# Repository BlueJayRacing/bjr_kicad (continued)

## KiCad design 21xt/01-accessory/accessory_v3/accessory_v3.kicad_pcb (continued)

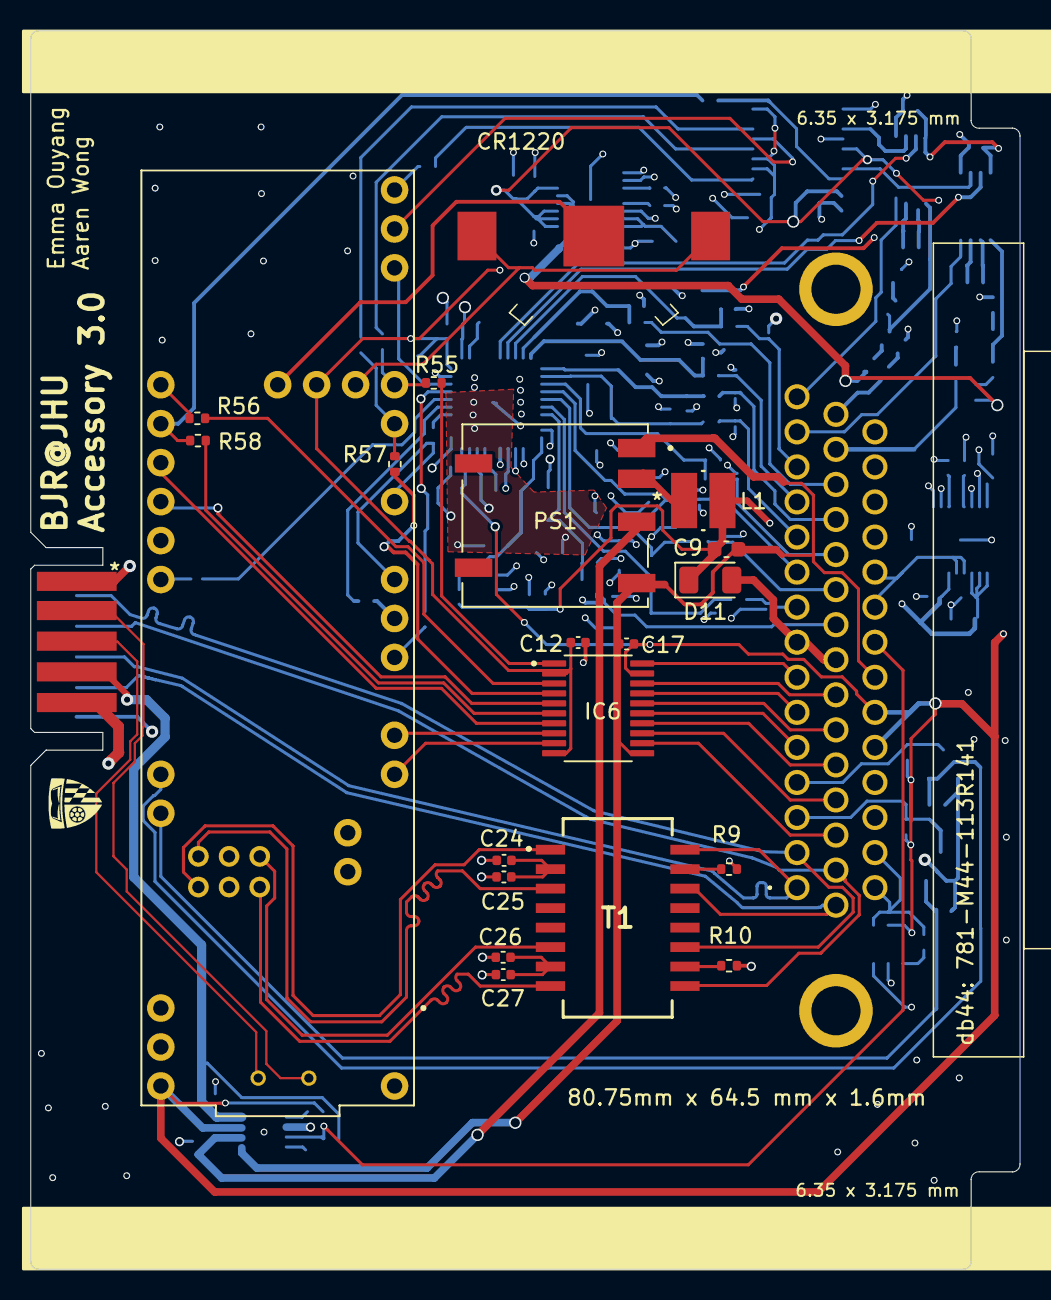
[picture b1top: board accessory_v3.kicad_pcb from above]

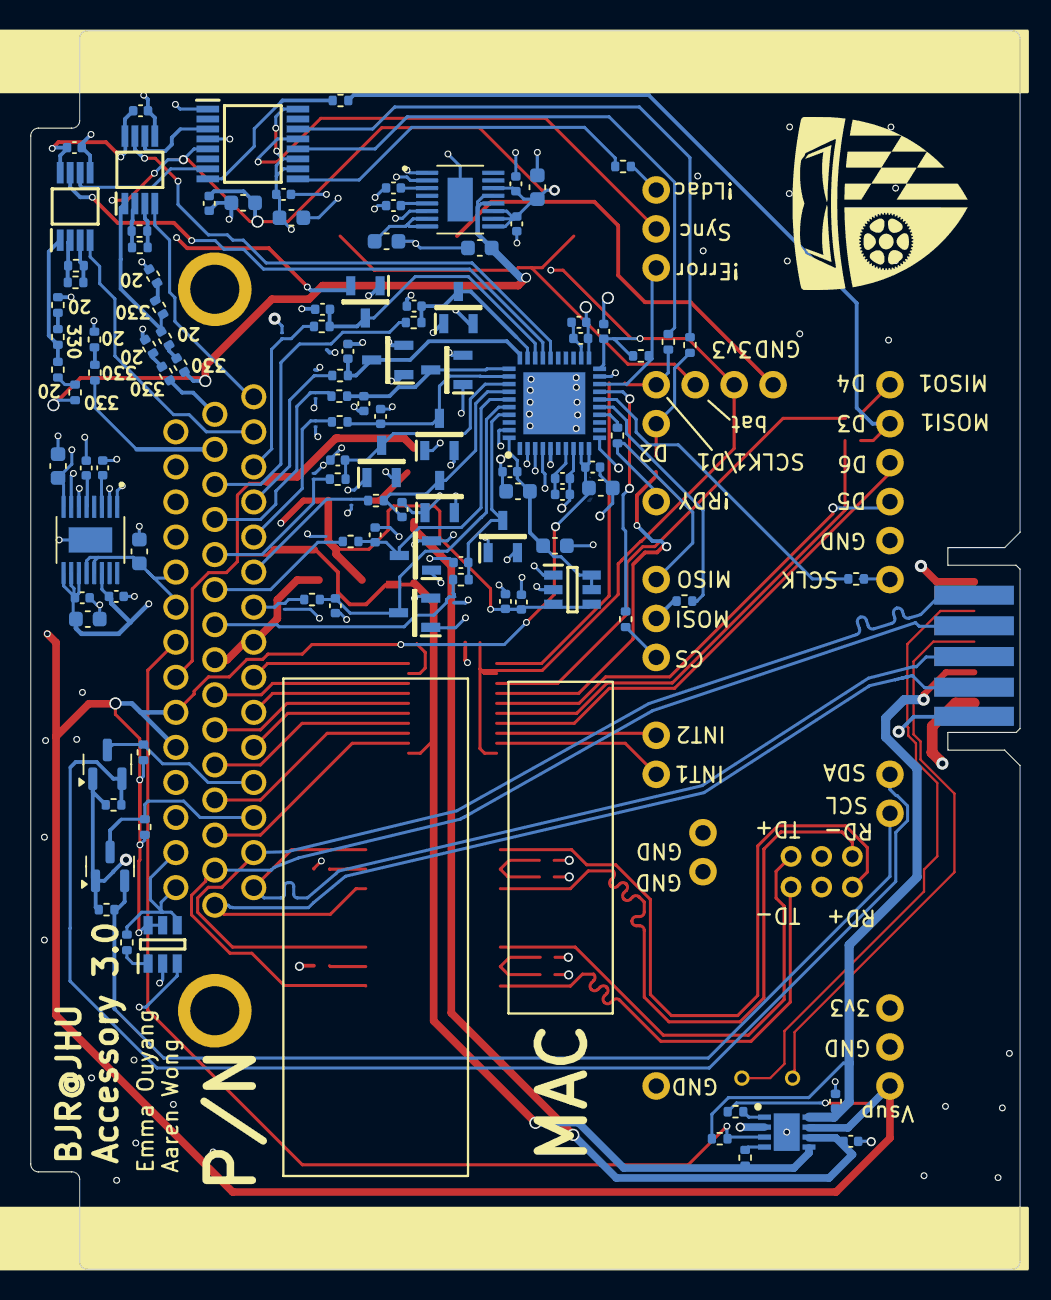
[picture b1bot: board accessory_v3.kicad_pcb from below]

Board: 4 copper layers, 64.5 x 80.8 mm, 141 parts (118 on the bottom side), 121 nets.

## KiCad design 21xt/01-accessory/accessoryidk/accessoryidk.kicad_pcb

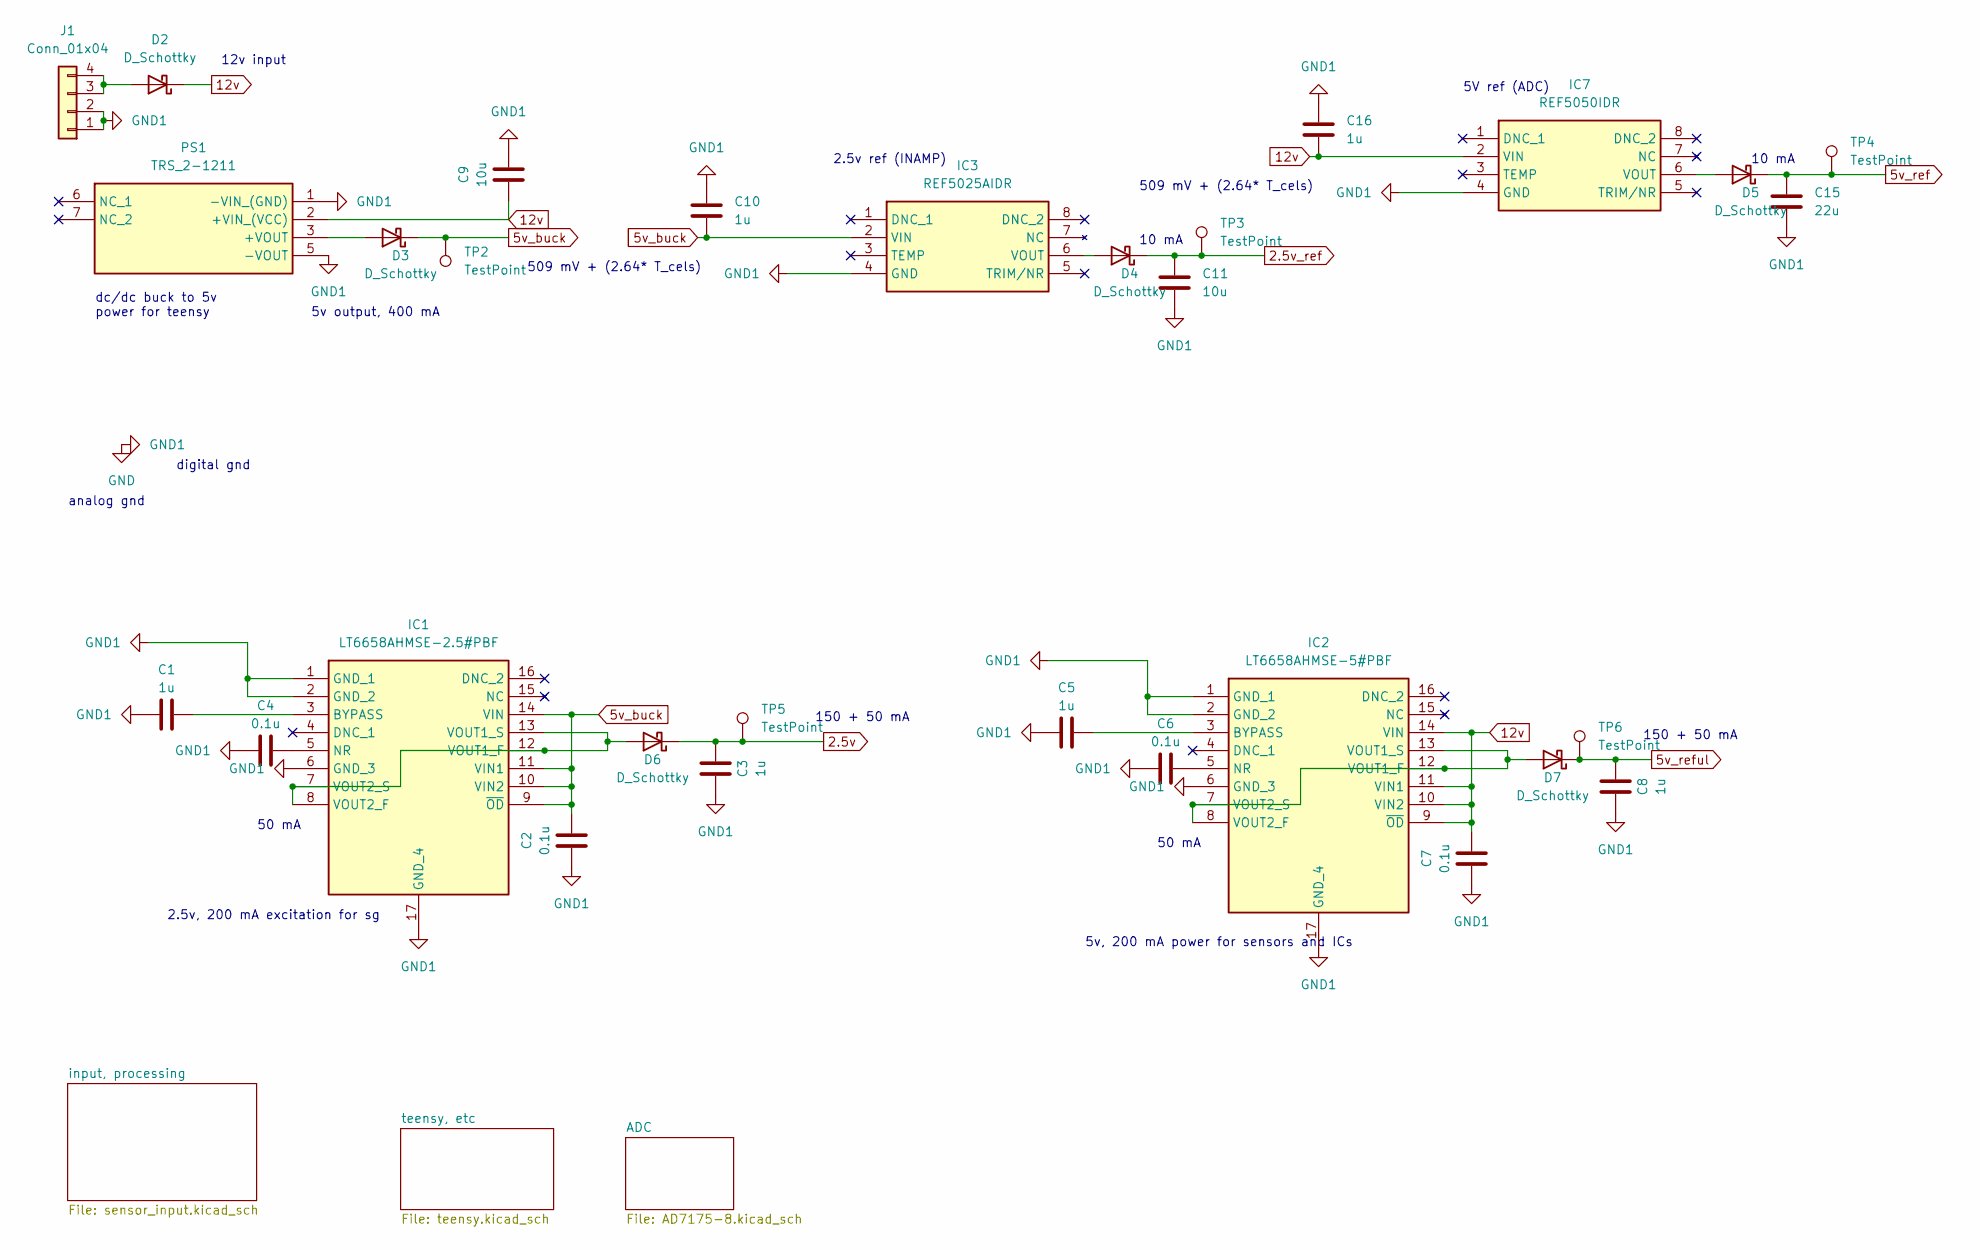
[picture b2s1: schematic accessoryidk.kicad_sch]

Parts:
C1, C3, C5, C8, C10, C16: 1u; C_0603_1608Metric
C2, C4, C6, C7: 0.1u; C_0603_1608Metric
C9: 10u; C_1206_3216Metric
C11: 10u; C_0603_1608Metric
C15: 22u; C_0603_1608Metric
D2: D_Schottky; D_1206_3216Metric
D3, D4, D5, D6, D7: D_Schottky; D_0603_1608Metric
IC1: LT6658AHMSE-2.5#PBF; SOP50P490X110-17N; Mouser Part Number 584-LT6658AHMSE5PBF
IC2: LT6658AHMSE-5#PBF; SOP50P490X110-17N; Mouser Part Number 584-LT6658AHMSE5PBF
IC3: REF5025AIDR; SOIC127P599X175-8N; Mouser Part Number 595-REF5050IDR
IC7: REF5050IDR; SOIC127P599X175-8N; Mouser Part Number 595-REF5050IDR
J1: Conn_01x04; JST_EH_B4B-EH-A_1x04_P2.50mm_Vertical
PS1: TRS_2-1211; CONV_TRS_2-2419; Mouser Part Number 495-TRS2-1211
TP2, TP3, TP4, TP5, TP6: TestPoint; TestPoint_Pad_2.0x2.0mm

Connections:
2.5v: C3.2, D6.1 (K), TP5.1; also elsewhere on the board
2.5v_ref: C11.1, D4.1 (K), TP3.1; also elsewhere on the board
5v_buck: C2.2, C10.1, D3.1 (K), IC1.9 (~OD), IC1.10 (VIN2), IC1.11 (VIN1), IC1.14 (VIN), IC3.2 (VIN), TP2.1; also elsewhere on the board
5v_ref: C15.1, D5.1 (K), TP4.1; also elsewhere on the board
5v_reful: C8.2, D7.1 (K), TP6.1; also elsewhere on the board
12v: C7.2, C9.1, C16.1, D2.1 (K), IC2.9 (~OD), IC2.10 (VIN2), IC2.11 (VIN1), IC2.14 (VIN), IC7.2 (VIN), PS1.2 (+VIN_(VCC)); also elsewhere on the board
unnamed: D2.2 (A), J1.3, J1.4
unnamed: D3.2 (A), PS1.3 (+VOUT)
unnamed: D4.2 (A), IC3.6 (VOUT)
unnamed: D5.2 (A), IC7.6 (VOUT)
unnamed: D6.2 (A), IC1.7 (VOUT2_S), IC1.8 (VOUT2_F), IC1.12 (VOUT1_F), IC1.13 (VOUT1_S)
unnamed: D7.2 (A), IC2.7 (VOUT2_S), IC2.8 (VOUT2_F), IC2.12 (VOUT1_F), IC2.13 (VOUT1_S)
unnamed: C1.2, IC1.3 (BYPASS)
unnamed: C4.2, IC1.5 (NR)
unnamed: C5.2, IC2.3 (BYPASS)
unnamed: C6.2, IC2.5 (NR)
usb_gnd: C1.1, C2.1, C3.1, C4.1, C5.1, C6.1, C7.1, C8.1, C9.2, C10.2, C11.2, C15.2, C16.2, IC1.1 (GND_1), IC1.2 (GND_2), IC1.6 (GND_3), IC1.17 (GND_4), IC2.1 (GND_1), IC2.2 (GND_2), IC2.6 (GND_3), IC2.17 (GND_4), IC3.4 (GND), IC7.4 (GND), J1.1, J1.2, PS1.1 (-VIN_(GND)), PS1.5 (-VOUT); also elsewhere on the board

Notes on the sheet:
2.5v, 200 mA excitation for sg
150 + 50 mA
50 mA
10 mA
5V ref (ADC)
12v input
5v, 200 mA power for sensors and ICs
2.5v ref (INAMP)
digital gnd
analog gnd
dc/dc buck to 5v power for teensy
5v output, 400 mA
509 mV + (2.64* T_cels)

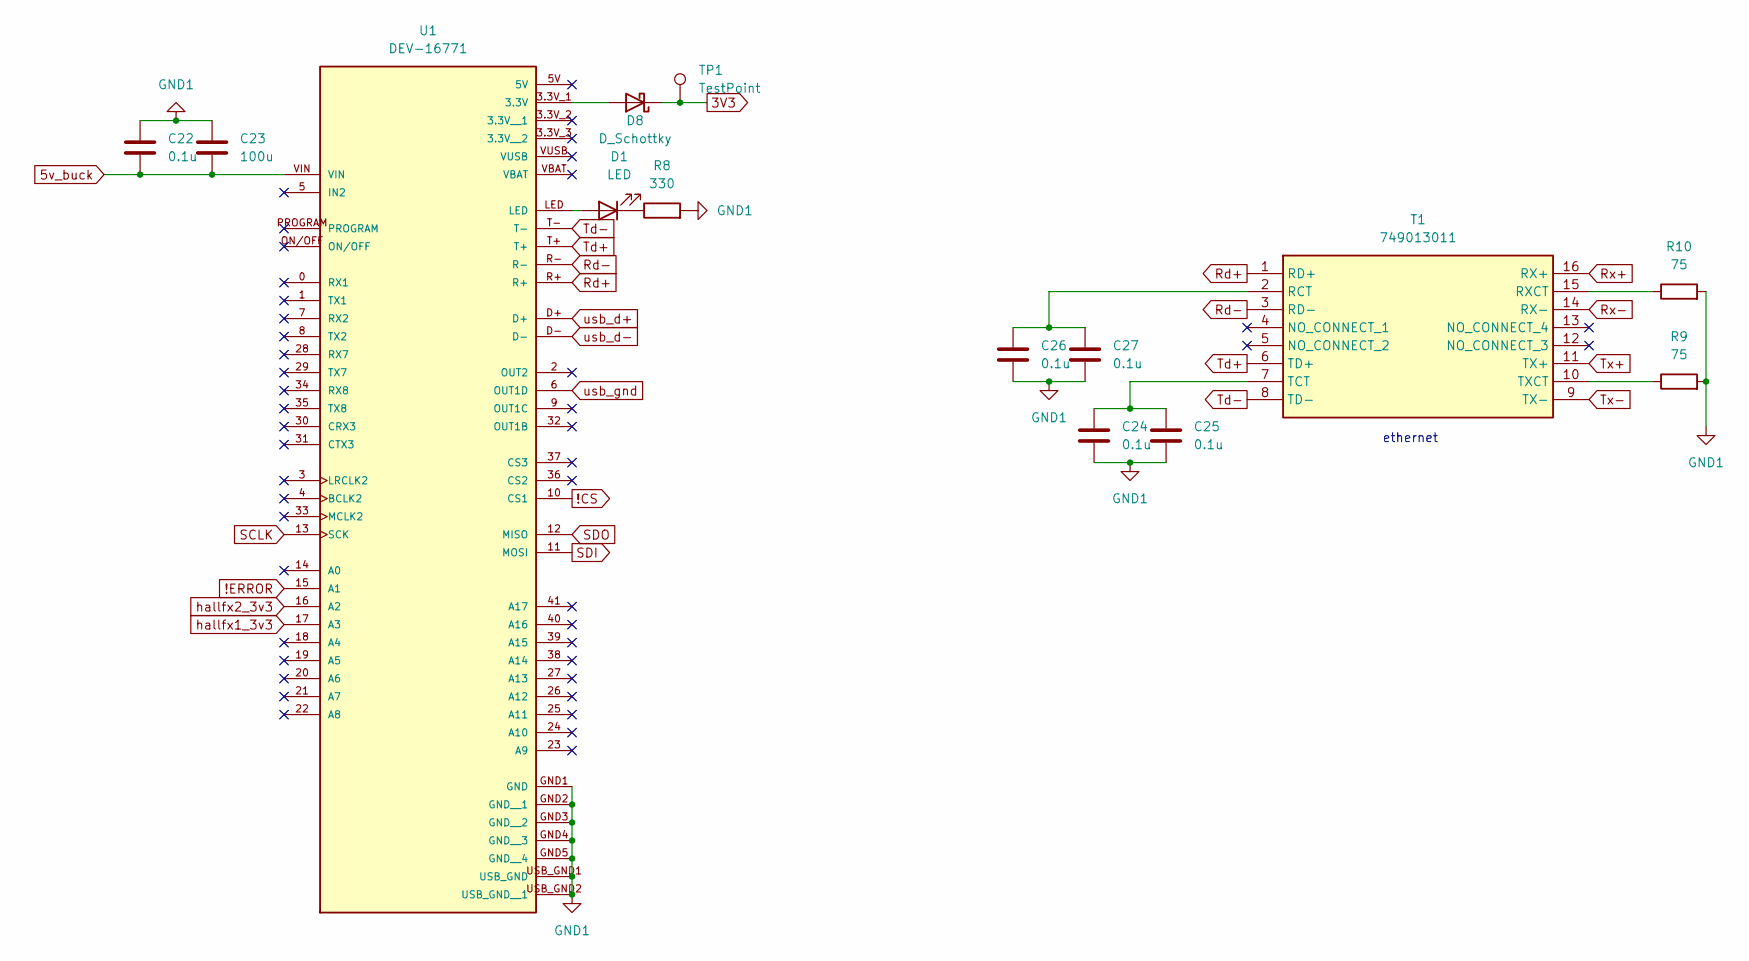
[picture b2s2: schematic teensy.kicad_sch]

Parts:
C22, C24, C25, C26, C27: 0.1u; C_0603_1608Metric
C23: 100u; C_1206_3216Metric
D1: LED; D_0603_1608Metric
D8: D_Schottky; D_0603_1608Metric
R8: 330; R_0603_1608Metric
R9, R10: 75; R_0603_1608Metric
T1: 749013011; Mouser Part Number 710-749013011
TP1: TestPoint; TestPoint_Pad_2.0x2.0mm
U1: DEV-16771; MODULE_DEV-16771; PARTREV 4.1

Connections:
3V3: D8.1 (K), TP1.1; also elsewhere on the board
5v_buck: C22.2, C23.2, U1.VIN; also elsewhere on the board
!CS: U1.10 (CS1); also elsewhere on the board
!ERROR: U1.15 (A1); also elsewhere on the board
unnamed: D1.2 (A), U1.LED
unnamed: D1.1 (K), R8.1
unnamed: D8.2 (A), U1.3.3V_1 (3.3V)
unnamed: C26.1, C27.1, T1.2 (RCT)
unnamed: R10.1, T1.15 (RXCT)
unnamed: C24.1, C25.1, T1.7 (TCT)
unnamed: R9.1, T1.10 (TXCT)
Rd+: T1.1 (RD+), U1.R+
Rd-: T1.3 (RD-), U1.R-
Rx+: T1.16 (RX+); also elsewhere on the board
Rx-: T1.14 (RX-); also elsewhere on the board
SCLK: U1.13 (SCK); also elsewhere on the board
SDI: U1.11 (MOSI); also elsewhere on the board
SDO: U1.12 (MISO); also elsewhere on the board
Td+: T1.6 (TD+), U1.T+
Td-: T1.8 (TD-), U1.T-
Tx+: T1.11 (TX+); also elsewhere on the board
Tx-: T1.9 (TX-); also elsewhere on the board
usb_d+: U1.D+; also elsewhere on the board
usb_d-: U1.D-; also elsewhere on the board
usb_gnd: C22.1, C23.1, C24.2, C25.2, C26.2, C27.2, R8.2, R9.2, R10.2, U1.6 (OUT1D), U1.GND1 (GND), U1.GND2 (GND__1), U1.GND3 (GND__2), U1.GND4 (GND__3), U1.GND5 (GND__4), U1.USB_GND1 (USB_GND), U1.USB_GND2 (USB_GND__1); also elsewhere on the board

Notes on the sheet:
ethernet

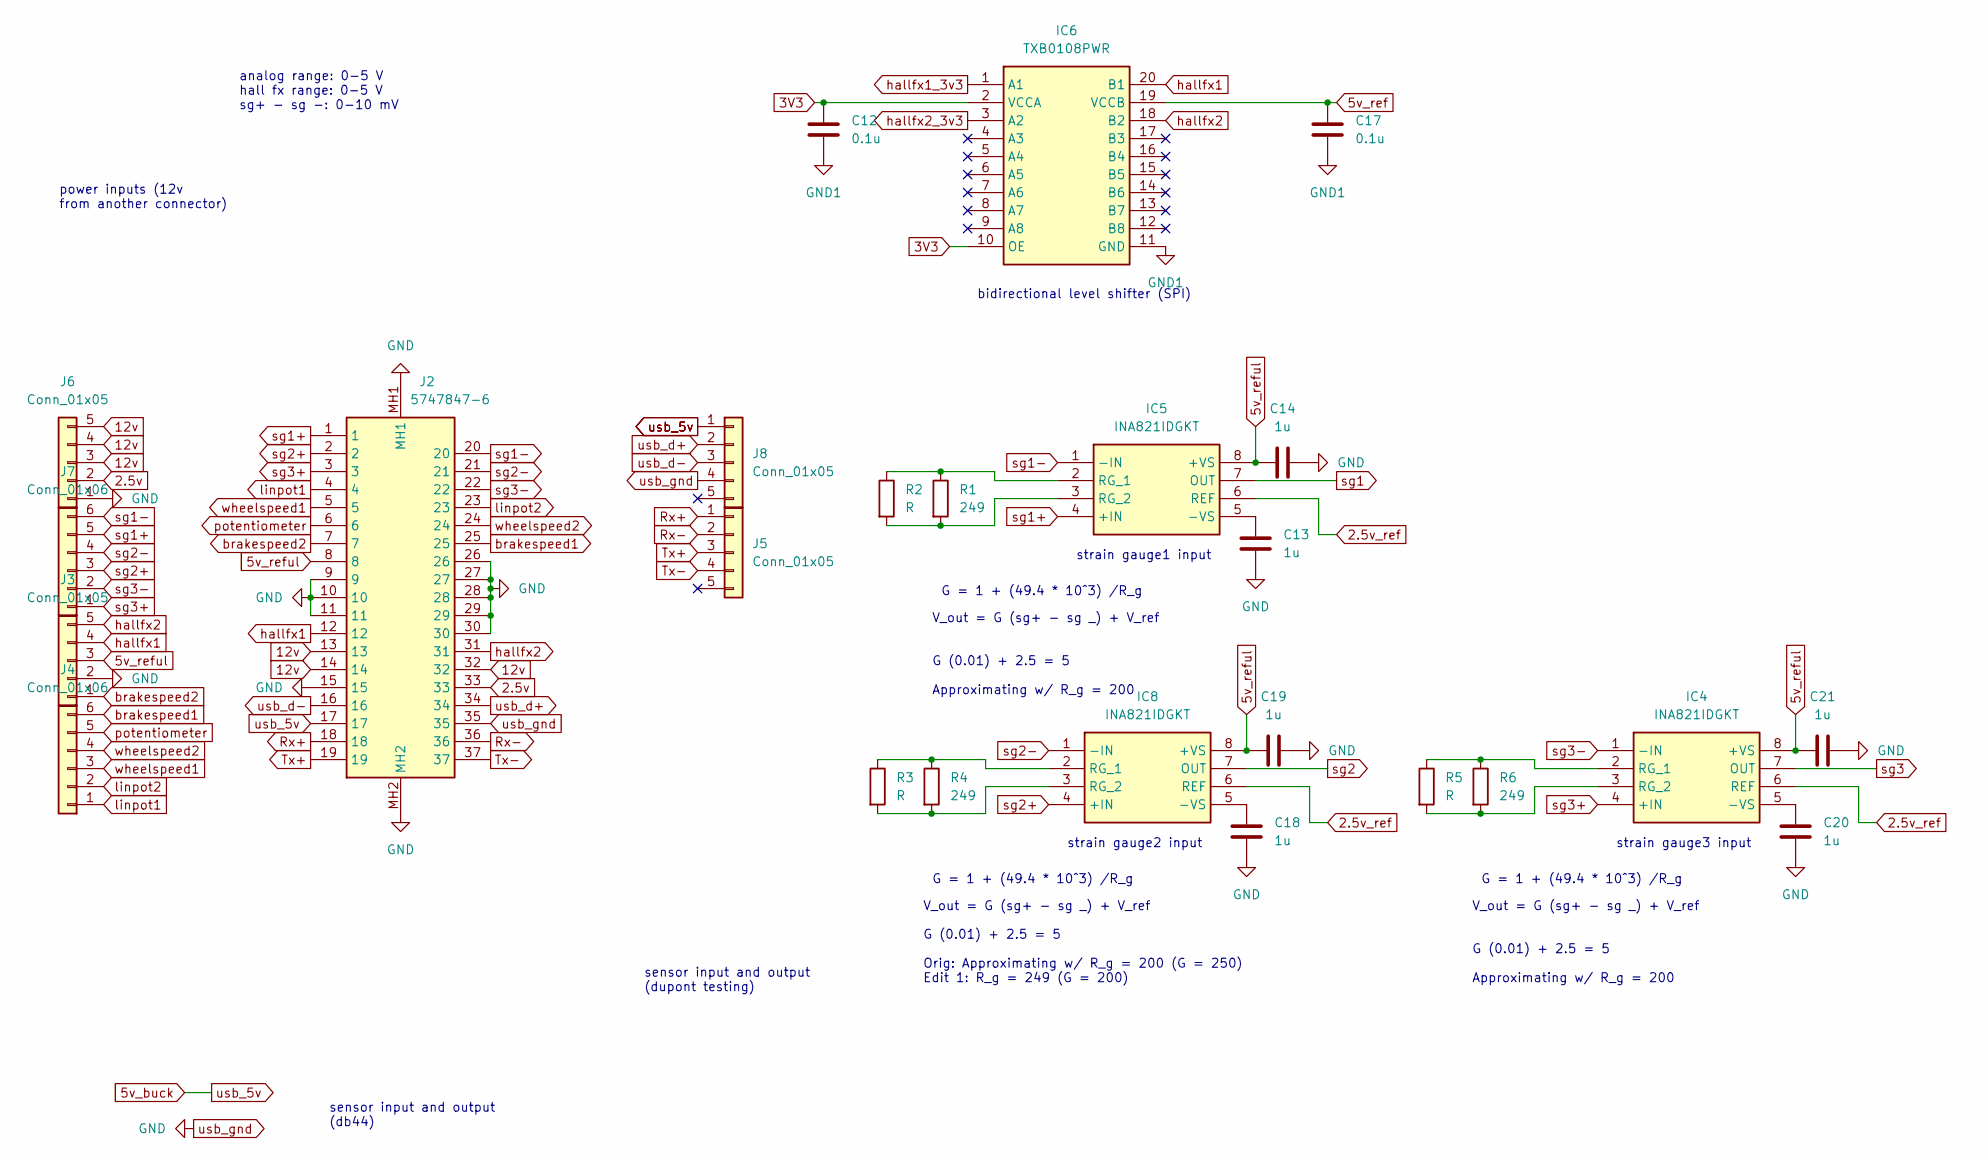
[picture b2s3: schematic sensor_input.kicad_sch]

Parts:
C12, C17: 0.1u; C_0603_1608Metric
C13, C14, C18, C19, C20, C21: 1u; C_0603_1608Metric
IC4, IC5, IC8: INA821IDGKT; SOP65P490X110-8N; Mouser Part Number 595-INA821IDGKT
IC6: TXB0108PWR; SOP65P640X120-20N; Mouser Part Number 595-TXB0108PWR
J2: 5747847-6; 57478476; Manufacturer_Part_Number 5747847-6; Mouser Part Number 571-5747847-6
J3, J5, J6, J8: Conn_01x05; JST_EH_B5B-EH-A_1x05_P2.50mm_Vertical
J4, J7: Conn_01x06; JST_EH_B6B-EH-A_1x06_P2.50mm_Vertical
R1, R4, R6: 249; R_0603_1608Metric
R2, R3, R5: R; R_0603_1608Metric

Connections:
2.5v: J2.33, J6.2; also elsewhere on the board
2.5v_ref: IC4.6 (REF), IC5.6 (REF), IC8.6 (REF); also elsewhere on the board
3V3: C12.1, IC6.2 (VCCA), IC6.10 (OE); also elsewhere on the board
5v_buck: J2.17, J8.1; also elsewhere on the board
5v_ref: C17.1, IC6.19 (VCCB); also elsewhere on the board
5v_reful: C14.1, C19.1, C21.1, IC4.8 (+VS), IC5.8 (+VS), IC8.8 (+VS), J2.8, J3.3; also elsewhere on the board
12v: J2.13, J2.14, J2.32, J6.3, J6.4, J6.5; also elsewhere on the board
unnamed: C20.1, IC4.5 (-VS)
unnamed: IC4.2 (RG_1), R5.1, R6.1
unnamed: IC4.3 (RG_2), R5.2, R6.2
unnamed: C13.1, IC5.5 (-VS)
unnamed: IC5.2 (RG_1), R1.1, R2.1
unnamed: IC5.3 (RG_2), R1.2, R2.2
unnamed: C18.1, IC8.5 (-VS)
unnamed: IC8.2 (RG_1), R3.1, R4.1
unnamed: IC8.3 (RG_2), R3.2, R4.2
Rx+: J2.18, J5.1; also elsewhere on the board
Rx-: J2.36, J5.2; also elsewhere on the board
Tx+: J2.19, J5.3; also elsewhere on the board
Tx-: J2.37, J5.4; also elsewhere on the board
brakespeed1: J2.25, J4.6; also elsewhere on the board
brakespeed2: J2.7, J3.1; also elsewhere on the board
hallfx1: IC6.20 (B1), J2.12, J3.4
hallfx2: IC6.18 (B2), J2.31, J3.5
linpot1: J2.4, J4.1; also elsewhere on the board
linpot2: J2.23, J4.2; also elsewhere on the board
potentiometer: J2.6, J4.5; also elsewhere on the board
sg1: IC5.7 (OUT); also elsewhere on the board
sg1+: IC5.4 (+IN), J2.1, J7.5
sg1-: IC5.1 (-IN), J2.20, J7.6
sg2: IC8.7 (OUT); also elsewhere on the board
sg2+: IC8.4 (+IN), J2.2, J7.3
sg2-: IC8.1 (-IN), J2.21, J7.4
sg3: IC4.7 (OUT); also elsewhere on the board
sg3+: IC4.4 (+IN), J2.3, J7.1
sg3-: IC4.1 (-IN), J2.22, J7.2
usb_d+: J2.34, J8.2; also elsewhere on the board
usb_d-: J2.16, J8.3; also elsewhere on the board
usb_gnd: C12.2, C13.2, C14.2, C17.2, C18.2, C19.2, C20.2, C21.2, IC6.11 (GND), J2.9, J2.10, J2.11, J2.15, J2.26, J2.27, J2.28, J2.29, J2.30, J2.35, J2.MH1, J2.MH2, J3.2, J6.1, J8.4; also elsewhere on the board
wheelspeed1: J2.5, J4.3; also elsewhere on the board
wheelspeed2: J2.24, J4.4; also elsewhere on the board

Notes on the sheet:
bidirectional level shifter (SPI)
power inputs (12v from another connector)
strain gauge3 input
strain gauge1 input
G = 1 + (49.4 * 10^3) /R_g
sensor input and output (db44)
strain gauge2 input
analog range: 0-5 V hall fx range: 0-5 V sg+ - sg -: 0-10 mV
V_out = G (sg+ - sg _) + V_ref
G (0.01) + 2.5 = 5 Approximating w/ R_g = 200
G (0.01) + 2.5 = 5 Orig: Approximating w/ R_g = 200 (G = 250) Edit 1: R_g = 249 (G = 200)
sensor input and output (dupont testing)

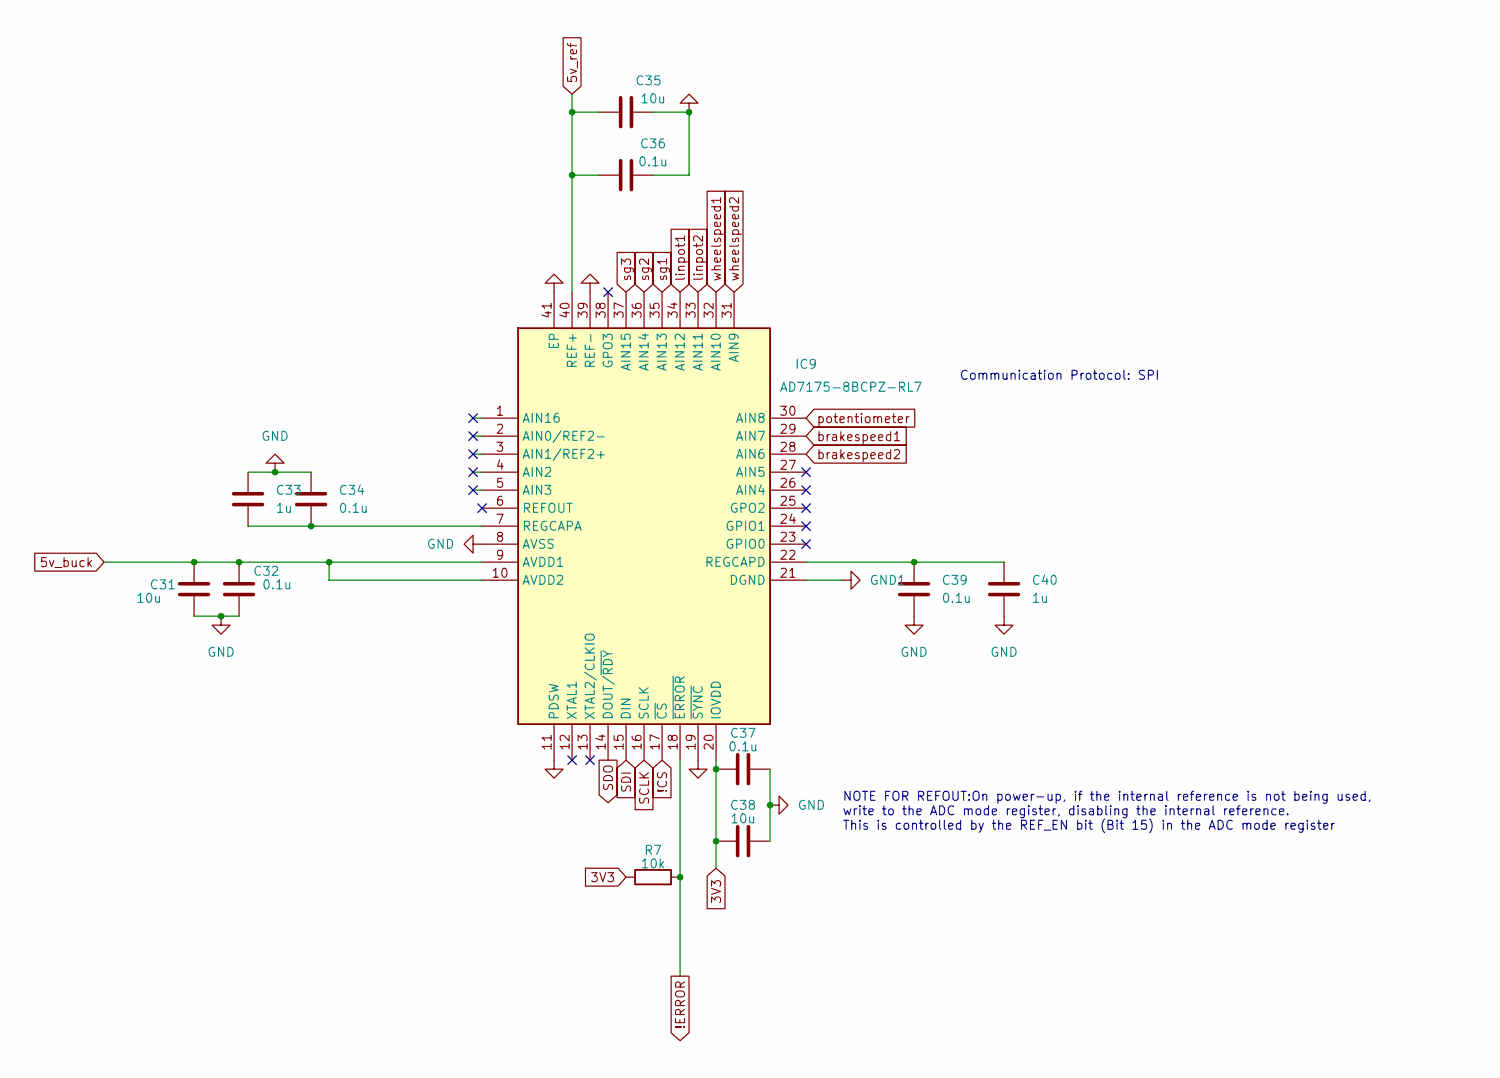
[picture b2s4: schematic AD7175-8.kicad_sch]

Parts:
C31, C35, C38: 10u; C_0603_1608Metric
C32, C34, C36, C37, C39: 0.1u; C_0603_1608Metric
C33, C40: 1u; C_0603_1608Metric
IC9: AD7175-8BCPZ-RL7; QFN50P600X600X80-41N; Mouser Part Number 584-AD7175-8BCPZ-RL7
R7: 10k; R_0603_1608Metric

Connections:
3V3: C37.1, C38.1, IC9.20 (IOVDD), R7.1; also elsewhere on the board
5v_buck: C31.1, C32.1, IC9.9 (AVDD1), IC9.10 (AVDD2); also elsewhere on the board
5v_ref: C35.1, C36.1, IC9.40 (REF+); also elsewhere on the board
!CS: IC9.17 (~CS); also elsewhere on the board
!ERROR: IC9.18 (~ERROR), R7.2; also elsewhere on the board
unnamed: C33.2, C34.2, IC9.7 (REGCAPA)
unnamed: C39.1, C40.1, IC9.22 (REGCAPD)
SCLK: IC9.16 (SCLK); also elsewhere on the board
SDI: IC9.15 (DIN); also elsewhere on the board
SDO: IC9.14 (DOUT/~RDY); also elsewhere on the board
brakespeed1: IC9.29 (AIN7); also elsewhere on the board
brakespeed2: IC9.28 (AIN6); also elsewhere on the board
linpot1: IC9.34 (AIN12); also elsewhere on the board
linpot2: IC9.33 (AIN11); also elsewhere on the board
potentiometer: IC9.30 (AIN8); also elsewhere on the board
sg1: IC9.35 (AIN13); also elsewhere on the board
sg2: IC9.36 (AIN14); also elsewhere on the board
sg3: IC9.37 (AIN15); also elsewhere on the board
usb_gnd: C31.2, C32.2, C33.1, C34.1, C35.2, C36.2, C37.2, C38.2, C39.2, C40.2, IC9.8 (AVSS), IC9.11 (PDSW), IC9.19 (~SYNC), IC9.21 (DGND), IC9.39 (REF-), IC9.41 (EP); also elsewhere on the board
wheelspeed1: IC9.32 (AIN10); also elsewhere on the board
wheelspeed2: IC9.31 (AIN9); also elsewhere on the board

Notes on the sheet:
NOTE FOR REFOUT:On power-up, if the internal reference is not being used, write to the ADC mode register, disabling the internal reference. This is controlled by the REF_EN bit (Bit 15) in the ADC mode register
Communication Protocol: SPI

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
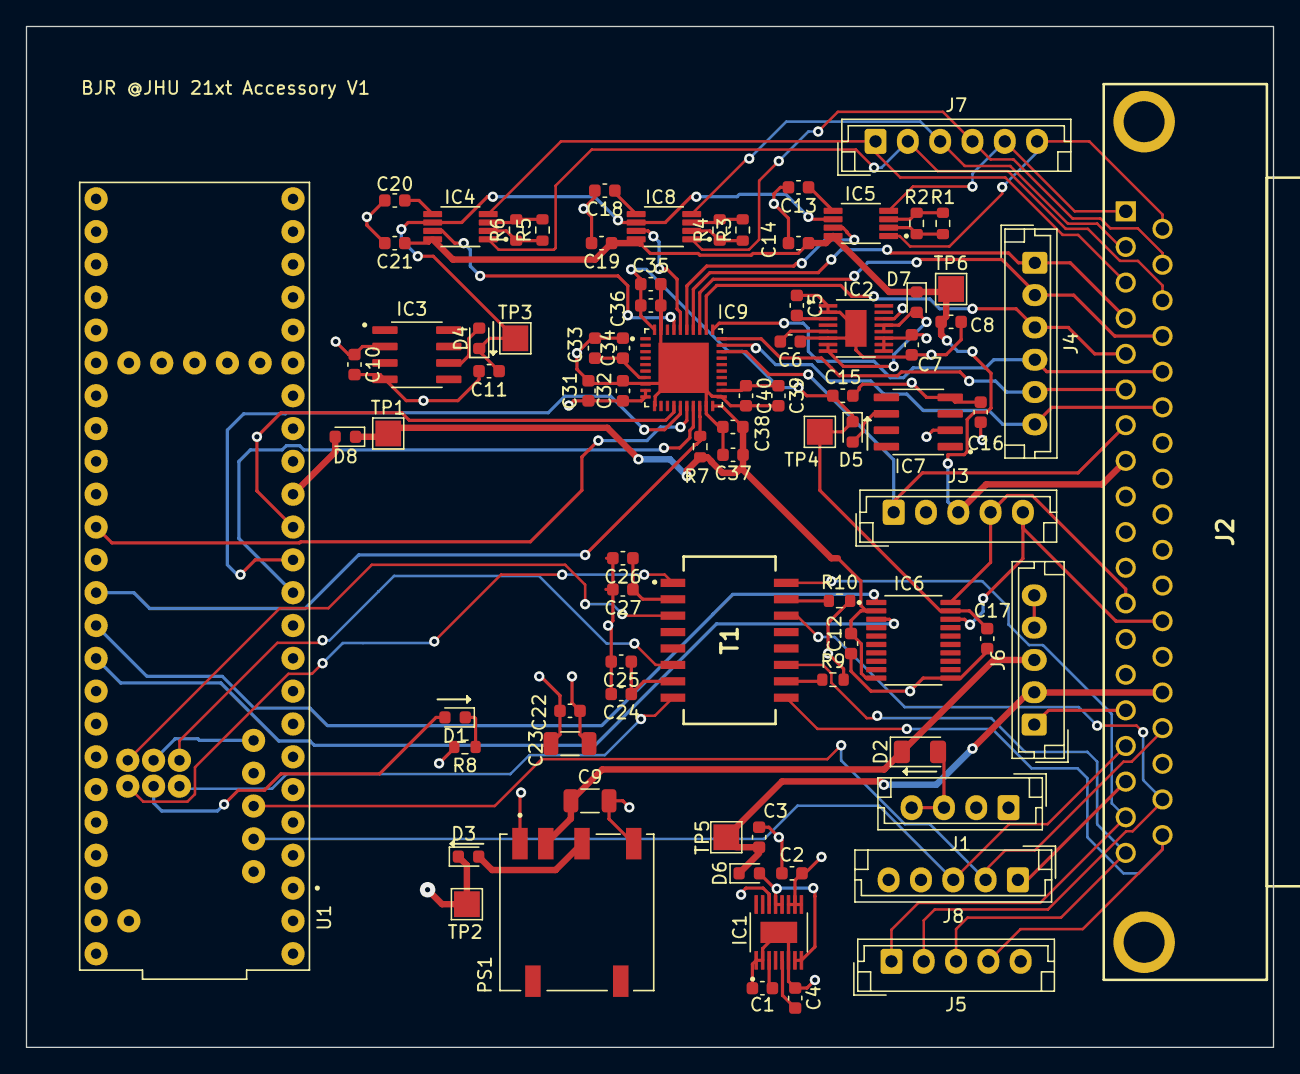
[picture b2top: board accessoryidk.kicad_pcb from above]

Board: 4 copper layers, 96.5 x 79.0 mm, 81 parts (0 on the bottom side), 71 nets.

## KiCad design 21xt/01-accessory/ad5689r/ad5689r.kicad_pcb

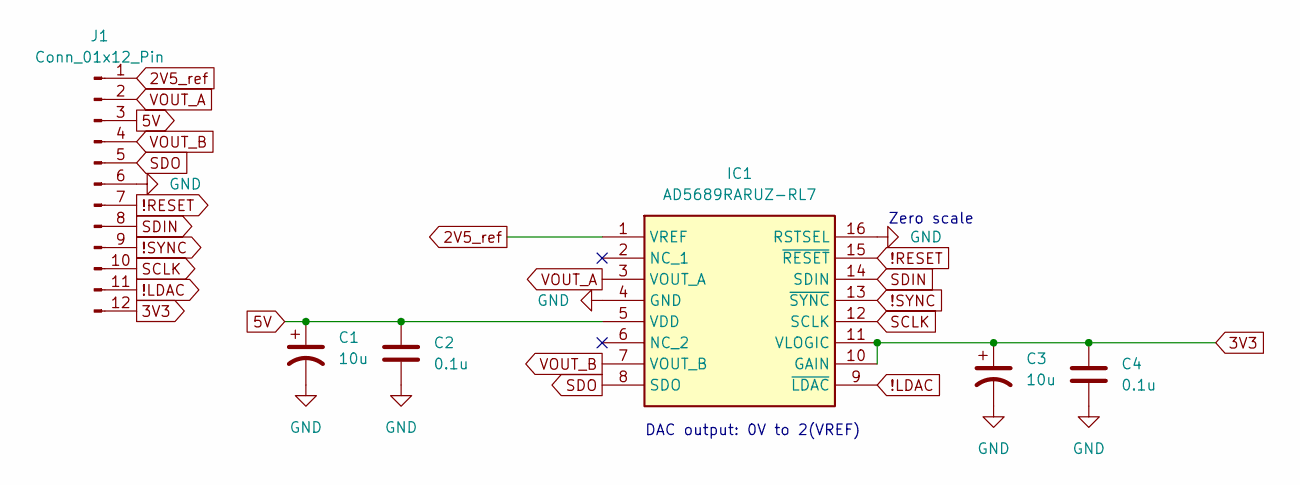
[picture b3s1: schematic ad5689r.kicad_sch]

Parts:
C1, C3: 10u; CAP_TPS_A_AVX
C2, C4: 0.1u; C_0603_1608Metric
IC1: AD5689RARUZ-RL7; SOP65P640X120-16N; Mouser Part Number 584-AD5689RARUZ-R7
J1: Conn_01x12_Pin; 6pin-6pin breadboard

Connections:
2V5_ref: IC1.1 (VREF), J1.1
3V3: C3.1, C4.1, IC1.10 (GAIN), IC1.11 (VLOGIC), J1.12
5V: C1.1, C2.1, IC1.5 (VDD), J1.3
!LDAC: IC1.9 (~LDAC), J1.11
!RESET: IC1.15 (~RESET), J1.7
!SYNC: IC1.13 (~SYNC), J1.9
GND: C1.2, C2.2, C3.2, C4.2, IC1.4 (GND), IC1.16 (RSTSEL), J1.6
SCLK: IC1.12 (SCLK), J1.10
SDIN: IC1.14 (SDIN), J1.8
SDO: IC1.8 (SDO), J1.5
VOUT_A: IC1.3 (VOUT_A), J1.2
VOUT_B: IC1.7 (VOUT_B), J1.4

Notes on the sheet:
DAC output: 0V to 2(VREF)
Zero scale

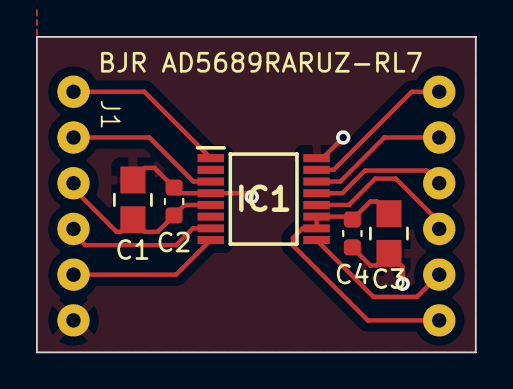
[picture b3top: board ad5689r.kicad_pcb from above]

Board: 2 copper layers, 24.4 x 17.5 mm, 6 parts (0 on the bottom side), 12 nets.

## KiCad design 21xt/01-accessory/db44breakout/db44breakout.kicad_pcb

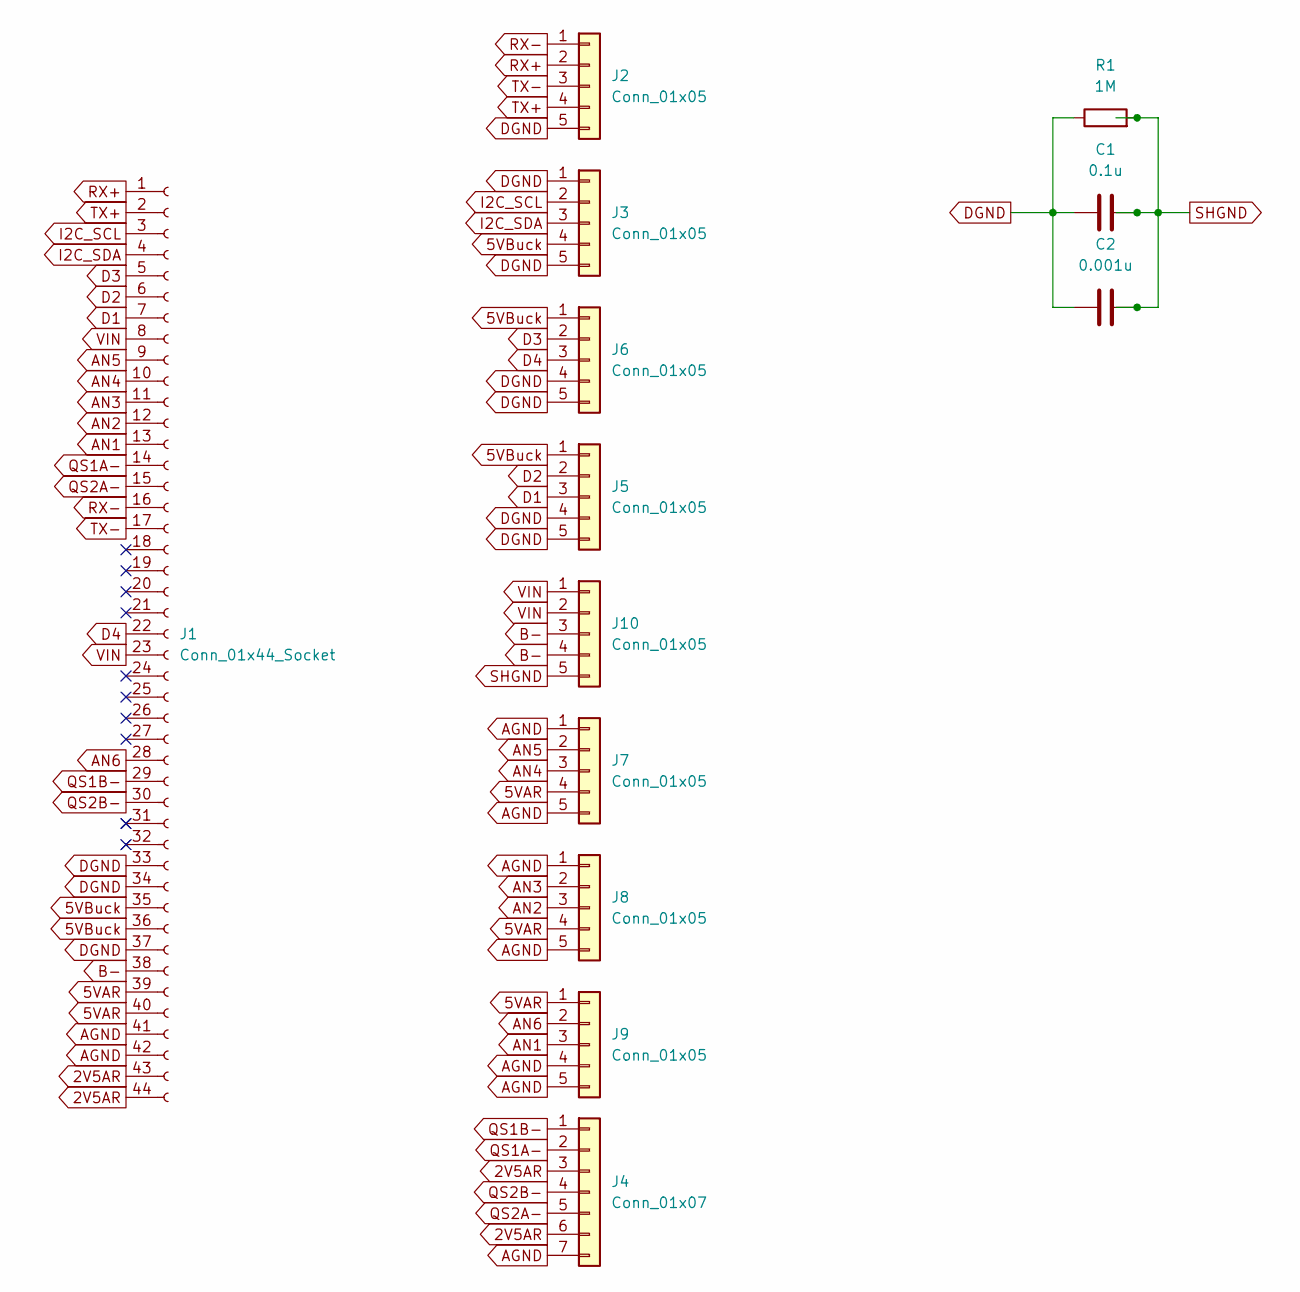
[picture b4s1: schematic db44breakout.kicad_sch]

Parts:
C1: 0.1u; C_0603_1608Metric
C2: 0.001u; C_0603_1608Metric
J1: Conn_01x44_Socket; AMPHENOL_ICD44S13E4GX00LF
J2, J6, J8, J10: Conn_01x05; 1x5WirePadsFront
J3, J5, J7, J9: Conn_01x05; 1x5WirePadsBack
J4: Conn_01x07; 1x7WirePads
R1: 1M; R_0603_1608Metric

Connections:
2V5AR: J1.43, J1.44, J4.3, J4.6
5VAR: J1.39, J1.40, J7.4, J8.4, J9.1
5VBuck: J1.35, J1.36, J3.4, J5.1, J6.1
AGND: J1.41, J1.42, J4.7, J7.1, J7.5, J8.1, J8.5, J9.4, J9.5
AN1: J1.13, J9.3
AN2: J1.12, J8.3
AN3: J1.11, J8.2
AN4: J1.10, J7.3
AN5: J1.9, J7.2
AN6: J1.28, J9.2
B-: J1.38, J10.3, J10.4
D1: J1.7, J5.3
D2: J1.6, J5.2
D3: J1.5, J6.2
D4: J1.22, J6.3
DGND: C1.1, C2.2, J1.33, J1.34, J1.37, J2.5, J3.1, J3.5, J5.4, J5.5, J6.4, J6.5, R1.1
I2C_SCL: J1.3, J3.2
I2C_SDA: J1.4, J3.3
QS1A-: J1.14, J4.2
QS1B-: J1.29, J4.1
QS2A-: J1.15, J4.5
QS2B-: J1.30, J4.4
RX+: J1.1, J2.2
RX-: J1.16, J2.1
SHGND: C1.2, C2.1, J10.5, R1.2
TX+: J1.2, J2.4
TX-: J1.17, J2.3
VIN: J1.8, J1.23, J10.1, J10.2

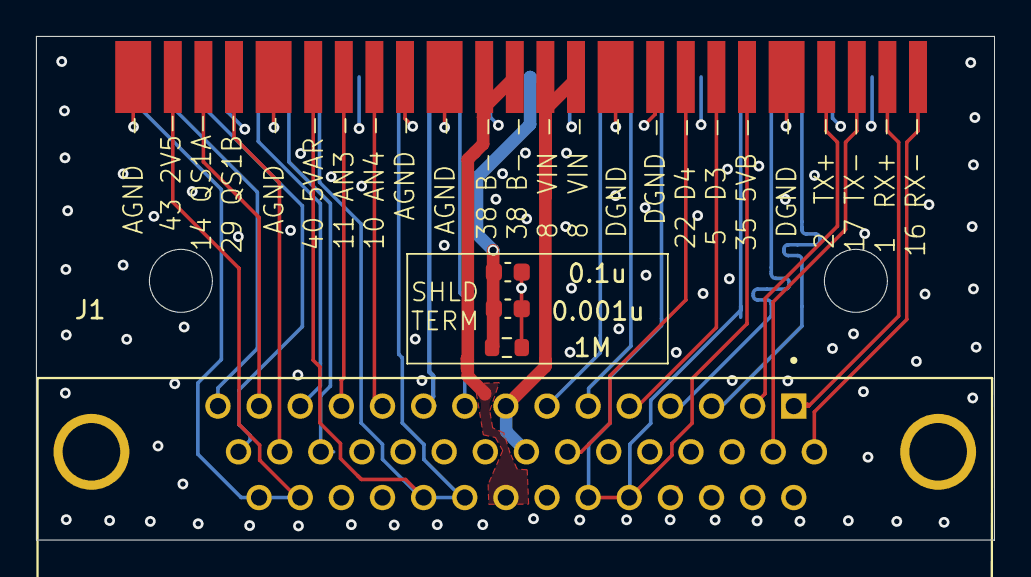
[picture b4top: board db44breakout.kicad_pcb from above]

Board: 4 copper layers, 53.2 x 28.0 mm, 13 parts (0 on the bottom side), 28 nets.
